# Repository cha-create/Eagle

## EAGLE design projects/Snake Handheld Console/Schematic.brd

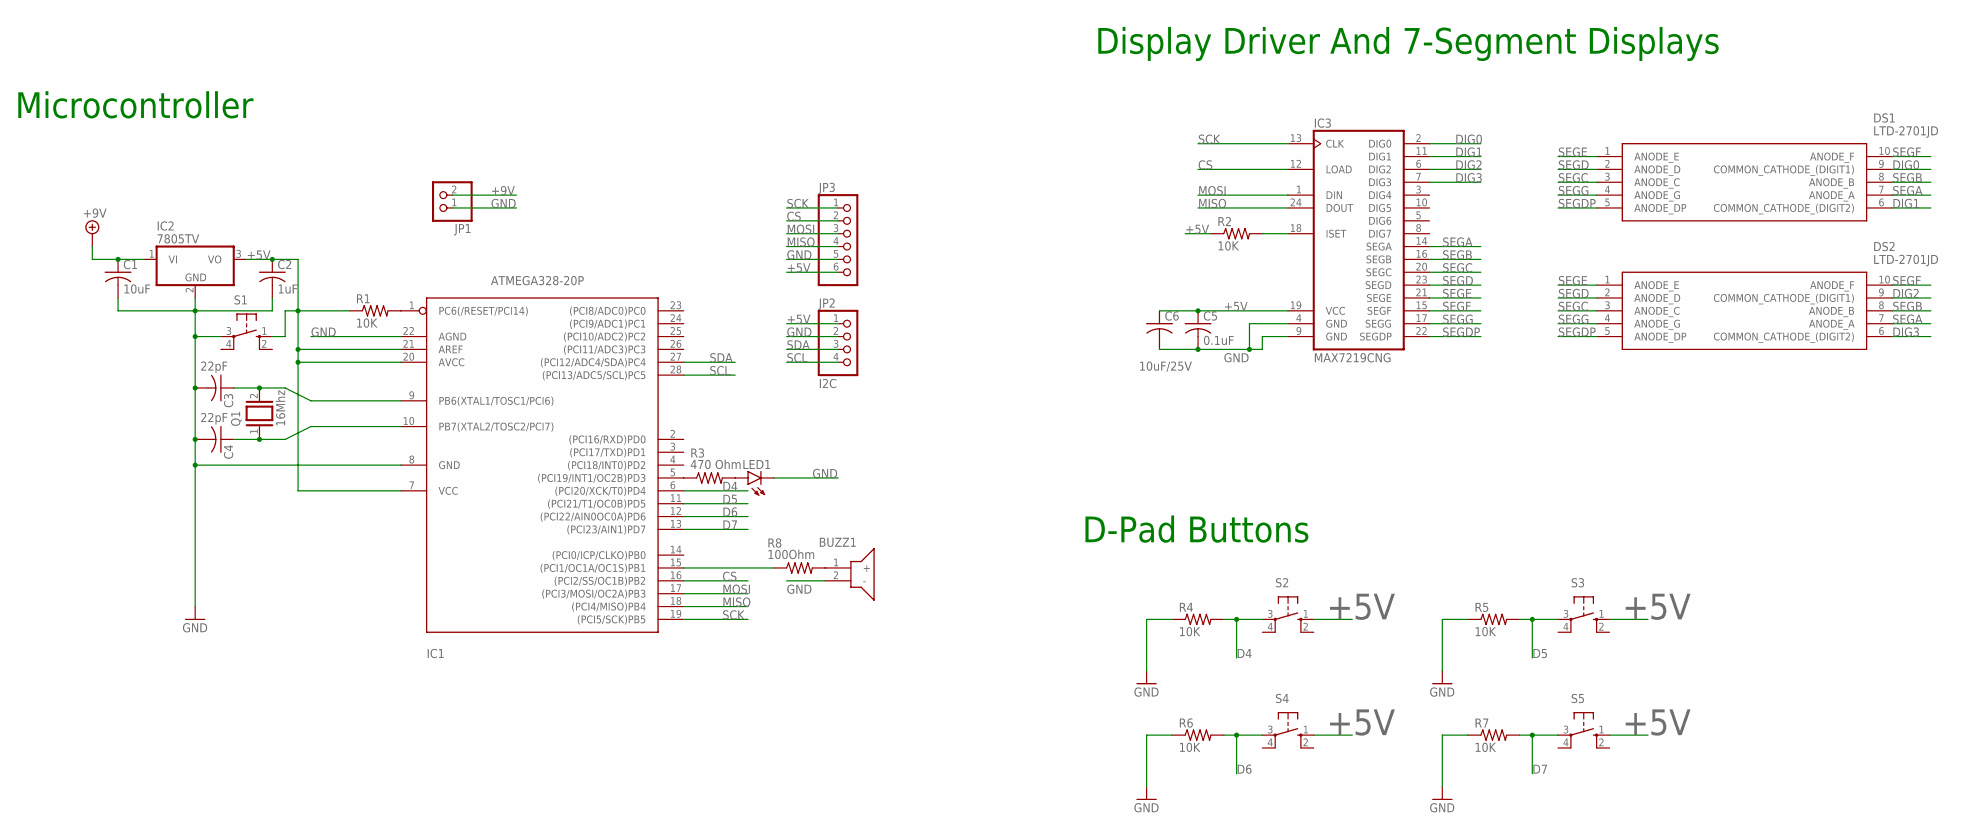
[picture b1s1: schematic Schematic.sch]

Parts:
BUZZ1: CMI-1295-0585T; CMI12950585T
C1: 10uF; C1206
C2: 1uF; C1206
C3, C4: 22pF; C1206
C5: 0.1uF; C1206
C6: 10uF/25V; C1206
DS1, DS2: LTD-2701JD; DIPS762W50P254L1502H635Q10N
IC1: ATMEGA328-20P; DIL28-3
IC2: 7805TV; TO220V
IC3: MAX7219CNG; DIL24-3
JP1: PINHD-1X2; 1X02
JP2: I2C; 1X04
JP3: PINHD-1X6; 1X06
LED1: LED5MM
Q1: 16Mhz; QS
R1, R2, R4, R5, R6, R7: 10K; R1206
R3: 470 Ohm; R1206
R8: 100Ohm; R1206
S1, S2, S3, S4, S5: 10-XX; B3F-10XX

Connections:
+5V: C2.1, C5.1, C6.1, IC1.7 (VCC), IC1.20 (AVCC), IC1.21 (AREF), IC2.3 (VO), IC3.19 (VCC), JP2.1, JP3.6, R1.1, R2.1, S1.1 (S), S2.1 (S), S3.1 (S), S4.1 (S), S5.1 (S)
+9V: C1.1, IC2.1 (VI), JP1.2
CS: IC1.16 ((PCI2/SS/OC1B)PB2), IC3.12 (LOAD), JP3.2
D4: IC1.6 ((PCI20/XCK/T0)PD4), R4.2, S2.3
D5: IC1.11 ((PCI21/T1/OC0B)PD5), R5.2, S3.3
D6: IC1.12 ((PCI22/AIN0OC0A)PD6), R6.2, S4.3
D7: IC1.13 ((PCI23/AIN1)PD7), R7.2, S5.3
DIG0: DS1.9 (COMMON_CATHODE_(DIGIT1)), IC3.2 (DIG0)
DIG1: DS1.6 (COMMON_CATHODE_(DIGIT2)), IC3.11 (DIG1)
DIG2: DS2.9 (COMMON_CATHODE_(DIGIT1)), IC3.6 (DIG2)
DIG3: DS2.6 (COMMON_CATHODE_(DIGIT2)), IC3.7 (DIG3)
GND: BUZZ1.2 (-), C1.2, C2.2, C3.2, C4.2, C5.2, C6.2, IC1.8 (GND), IC1.22 (AGND), IC2.2 (GND), IC3.4 (GND), IC3.9 (GND), JP1.1, JP2.2, JP3.5, LED1.K (C), R4.1, R5.1, R6.1, R7.1, S1.3
MISO: IC1.18 ((PCI4/MISO)PB4), IC3.24 (DOUT), JP3.4
MOSI: IC1.17 ((PCI3/MOSI/OC2A)PB3), IC3.1 (DIN), JP3.3
unnamed: IC3.18 (ISET), R2.2
unnamed: C3.1, IC1.9 (PB6(XTAL1/TOSC1/PCI6)), Q1.2
unnamed: C4.1, IC1.10 (PB7(XTAL2/TOSC2/PCI7)), Q1.1
unnamed: IC1.1 (PC6(/RESET/PCI14)), R1.2
unnamed: IC1.5 ((PCI19/INT1/OC2B)PD3), R3.1
unnamed: LED1.A, R3.2
unnamed: IC1.15 ((PCI1/OC1A/OC1S)PB1), R8.1
unnamed: BUZZ1.1 (+), R8.2
SCK: IC1.19 ((PCI5/SCK)PB5), IC3.13 (CLK), JP3.1
SCL: IC1.28 ((PCI13/ADC5/SCL)PC5), JP2.4
SDA: IC1.27 ((PCI12/ADC4/SDA)PC4), JP2.3
SEGA: DS1.7 (ANODE_A), DS2.7 (ANODE_A), IC3.14 (SEGA)
SEGB: DS1.8 (ANODE_B), DS2.8 (ANODE_B), IC3.16 (SEGB)
SEGC: DS1.3 (ANODE_C), DS2.3 (ANODE_C), IC3.20 (SEGC)
SEGD: DS1.2 (ANODE_D), DS2.2 (ANODE_D), IC3.23 (SEGD)
SEGDP: DS1.5 (ANODE_DP), DS2.5 (ANODE_DP), IC3.22 (SEGDP)
SEGE: DS1.1 (ANODE_E), DS2.1 (ANODE_E), IC3.21 (SEGE)
SEGF: DS1.10 (ANODE_F), DS2.10 (ANODE_F), IC3.15 (SEGF)
SEGG: DS1.4 (ANODE_G), DS2.4 (ANODE_G), IC3.17 (SEGG)

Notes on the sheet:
Display Driver And 7-Segment Displays
Microcontroller
D-Pad Buttons

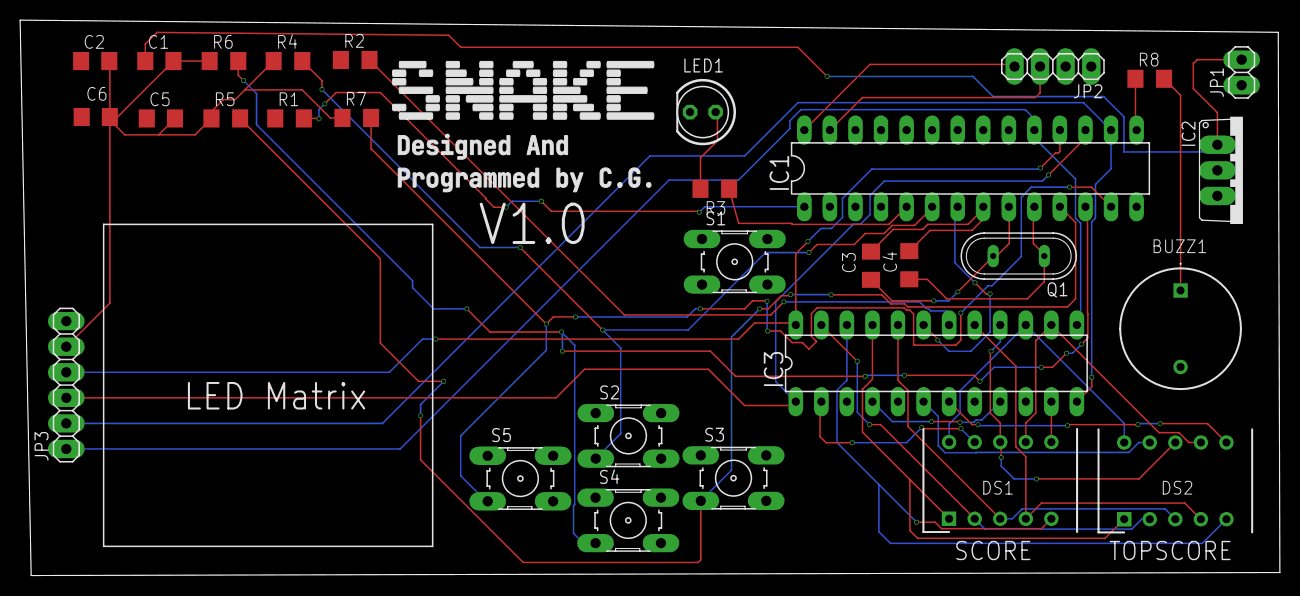
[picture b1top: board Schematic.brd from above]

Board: 2 copper layers, 125.2 x 55.2 mm, 30 parts (0 on the bottom side), 33 nets.

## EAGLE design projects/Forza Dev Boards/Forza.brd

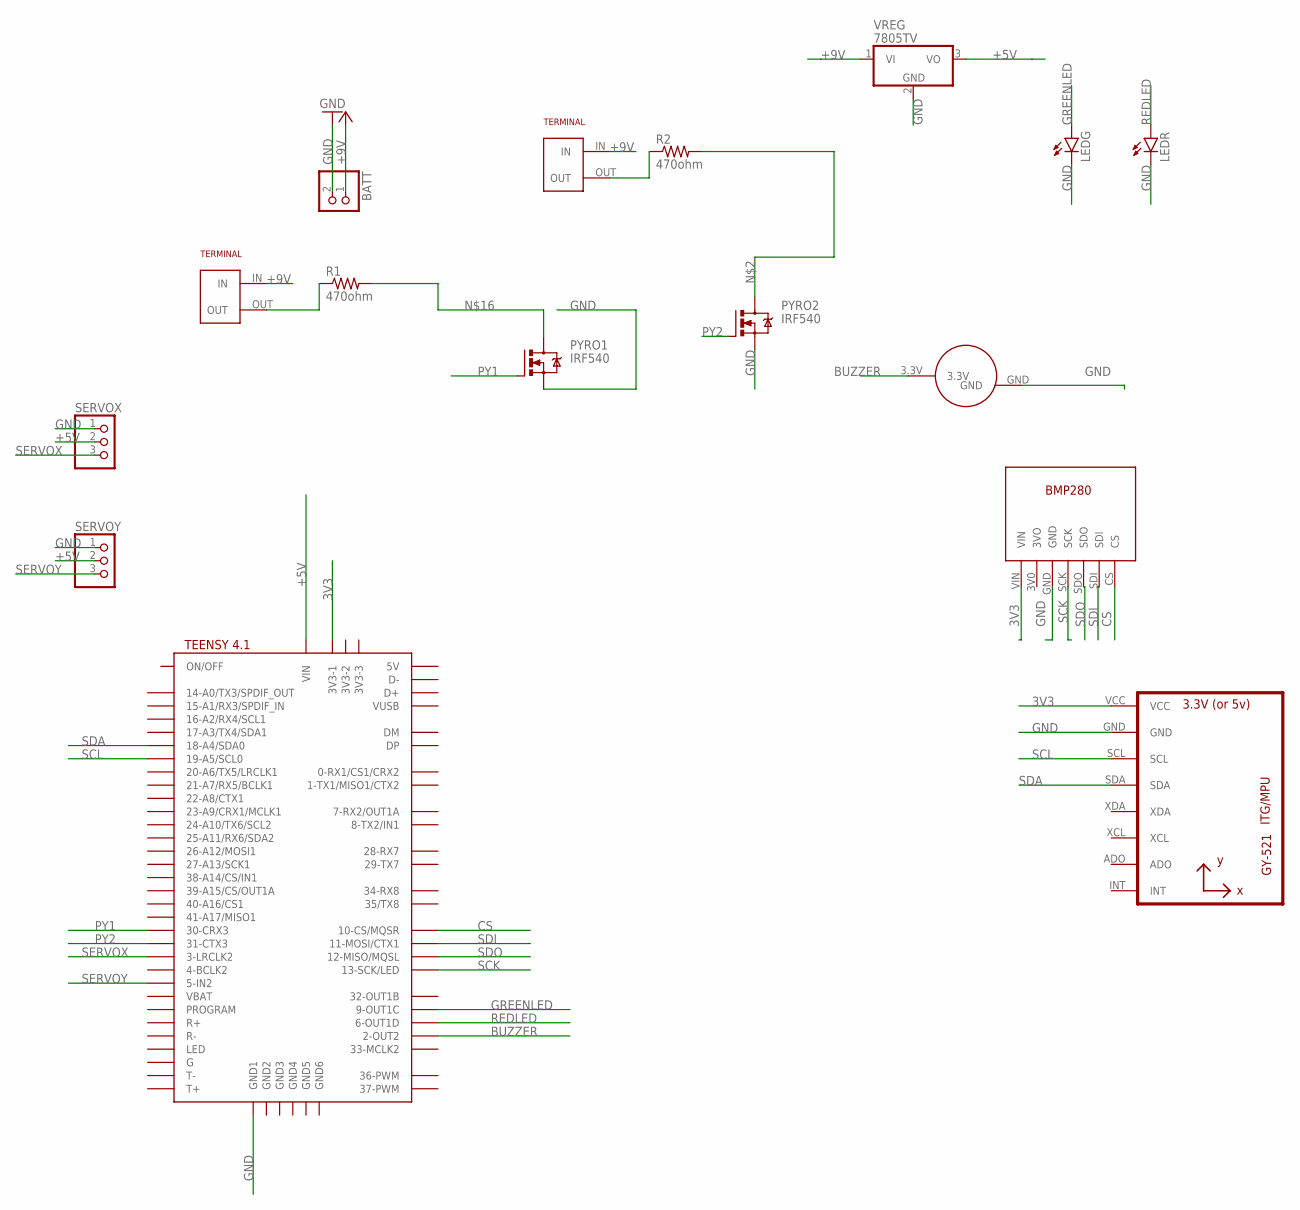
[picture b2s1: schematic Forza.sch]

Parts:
BATT: PINHD-1X2; 1X02
LEDG: LED5MM
LEDR: LED5MM
PY1, PY2: SCREWTERMINAL
PYRO1, PYRO2: IRF540; TO220BV
R1, R2: 470ohm; 0204/7
SERVOX: PINHD-1X3; 1X03
SERVOY: PINHD-1X3; 1X03
U1: GY-521MPU6050; GY-521
U$2: BUZZER
U$3: TEENSY41
U$4: BMP280
VREG: 7805TV; TO220V

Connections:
3V3: U1.VCC, U$3.3V3-1, U$4.VIN
+5V: SERVOX.2, SERVOY.2, U$3.VIN, VREG.3 (VO)
+9V: BATT.1, PY1.IN, PY2.IN, VREG.1 (VI)
BUZZER: U$2.3.3V, U$3.2-OUT2
CS: U$3.10-CS\MQSR (10-CS/MQSR), U$4.CS
GND: BATT.2, LEDG.K (C), LEDR.K (C), PYRO1.S, PYRO2.S, SERVOX.1, SERVOY.1, U1.GND, U$2.GND, U$3.GND1, U$4.GND, VREG.2 (GND)
GREENLED: LEDG.A, U$3.9-OUT1C
unnamed: PY1.OUT, R1.1
unnamed: PYRO2.D, R2.2
unnamed: PY2.OUT, R2.1
unnamed: PYRO1.D, R1.2
PY1: PYRO1.G, U$3.30-CRX3
PY2: PYRO2.G, U$3.31-CTX3
REDLED: LEDR.A, U$3.6-OUT1D
SCK: U$3.13-SCK/LED, U$4.SCK
SCL: U1.SCL, U$3.19-A5/SCL0
SDA: U1.SDA, U$3.18-A4/SDA0
SDI: U$3.11-MOSI/CTX1, U$4.SDI
SDO: U$3.12-MISO/MQSL, U$4.SDO
SERVOX: SERVOX.3, U$3.3-LRCLK2
SERVOY: SERVOY.3, U$3.5-IN2

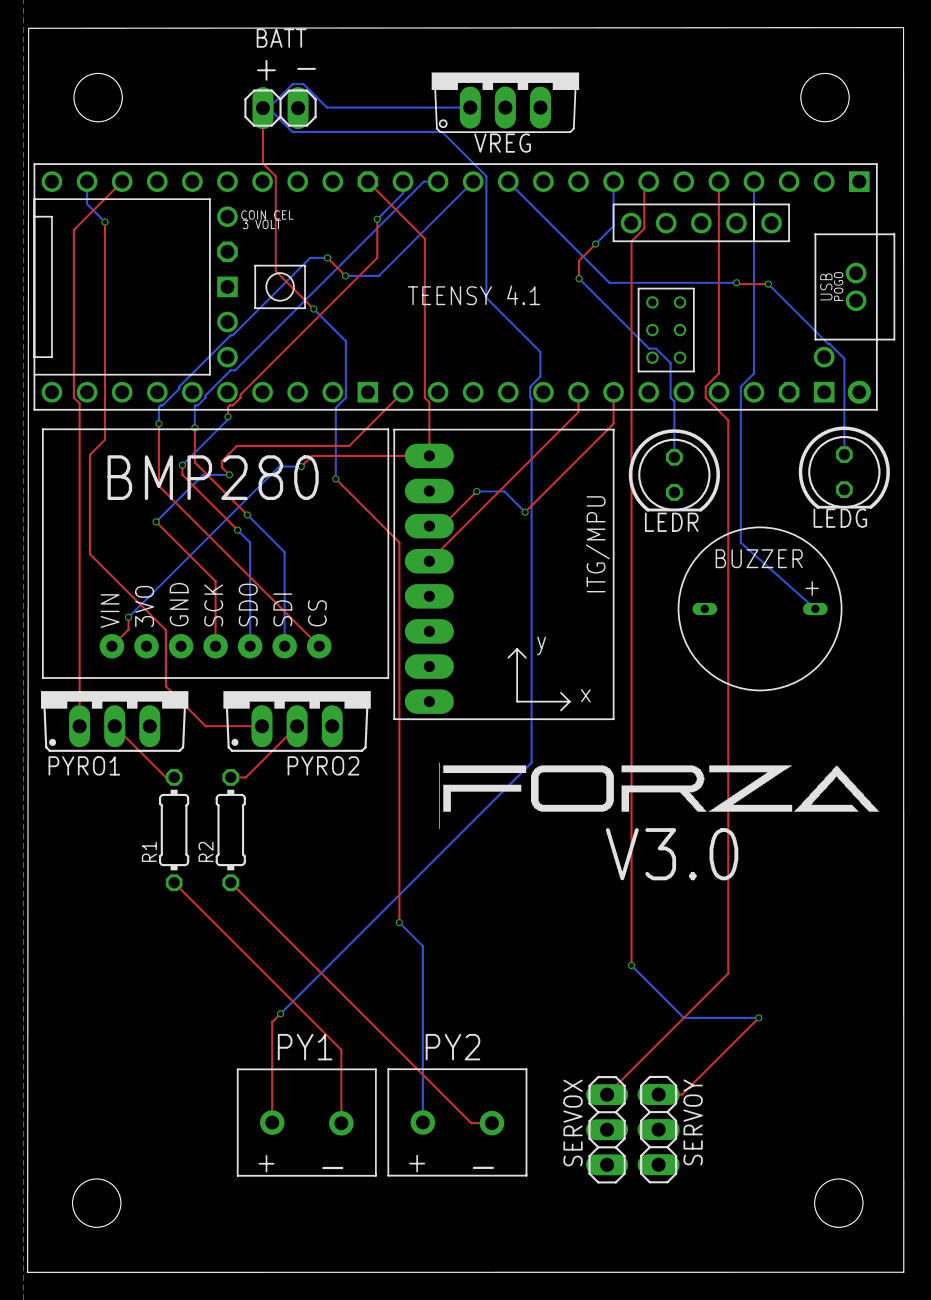
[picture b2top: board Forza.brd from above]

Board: 2 copper layers, 63.4 x 90.1 mm, 16 parts (0 on the bottom side), 21 nets.

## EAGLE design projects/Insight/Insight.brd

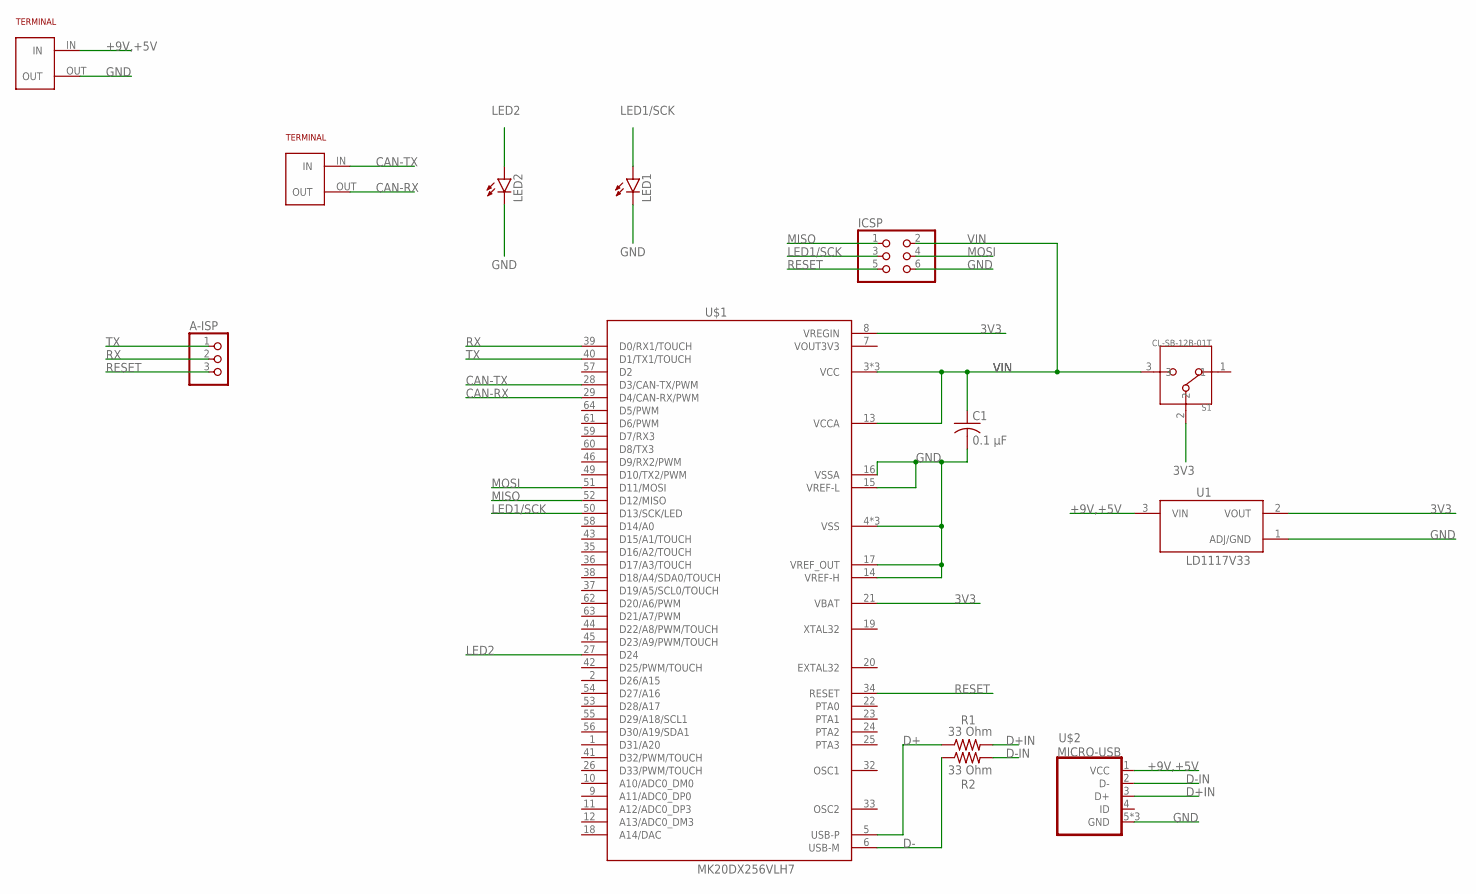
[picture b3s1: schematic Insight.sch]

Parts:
A-ISP: PINHD-1X3; 1X03
C1: 0.1 µF; C0805
ICSP: PINHD-2X3; 2X03
LED1, LED2: LED5MM
R1, R2: 33 Ohm; R1206
S1: CL-SB-12B-01T; CL-SB-12B
U1: LD1117V33; TO255P1020X450X1968-3
U$1: MK20DX256VLH7; QFP50P1200X1200X160-64N
U$2: MICRO-USB
U$3, U$4: SCREWTERMINAL

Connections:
3V3: S1.2, U1.2 (VOUT), U$1.8 (VREGIN), U$1.21 (VBAT)
+9V,+5V: U1.3 (VIN), U$2.1 (VCC), U$3.IN
CAN-RX: U$1.29 (D4/CAN-RX/PWM), U$4.OUT
CAN-TX: U$1.28 (D3/CAN-TX/PWM), U$4.IN
D+: R1.1, U$1.5 (USB-P)
D+IN: R1.2, U$2.3 (D+)
D-: R2.1, U$1.6 (USB-M)
D-IN: R2.2, U$2.2 (D-)
GND: C1.2, ICSP.6, LED1.K (C), LED2.K (C), U1.1 (ADJ/GND), U$1.4 (VSS), U$1.14 (VREF-H), U$1.15 (VREF-L), U$1.16 (VSSA), U$1.17 (VREF_OUT), U$1.31 (VSS), U$1.47 (VSS), U$2.5 (GND), U$2.GND1 (GND), U$2.GND2 (GND), U$3.OUT
LED1/SCK: ICSP.3, LED1.A, U$1.50 (D13/SCK/LED)
LED2: LED2.A, U$1.27 (D24)
MISO: ICSP.1, U$1.52 (D12/MISO)
MOSI: ICSP.4, U$1.51 (D11/MOSI)
RESET: A-ISP.3, ICSP.5, U$1.34 (RESET)
RX: A-ISP.2, U$1.39 (D0/RX1/TOUCH)
TX: A-ISP.1, U$1.40 (D1/TX1/TOUCH)
VIN: C1.1, ICSP.2, S1.3, U$1.3 (VCC), U$1.13 (VCCA), U$1.30 (VCC), U$1.48 (VCC)

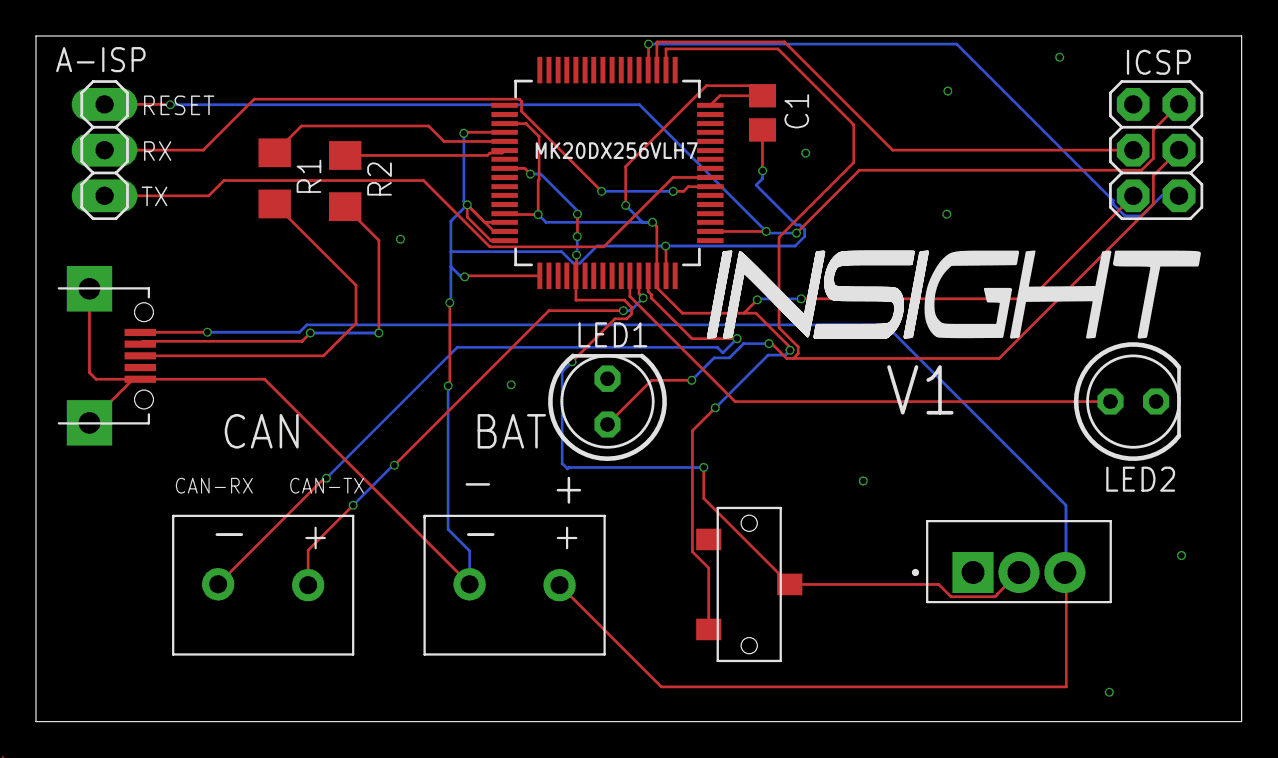
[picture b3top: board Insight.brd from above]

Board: 2 copper layers, 67.0 x 38.1 mm, 13 parts (0 on the bottom side), 17 nets.

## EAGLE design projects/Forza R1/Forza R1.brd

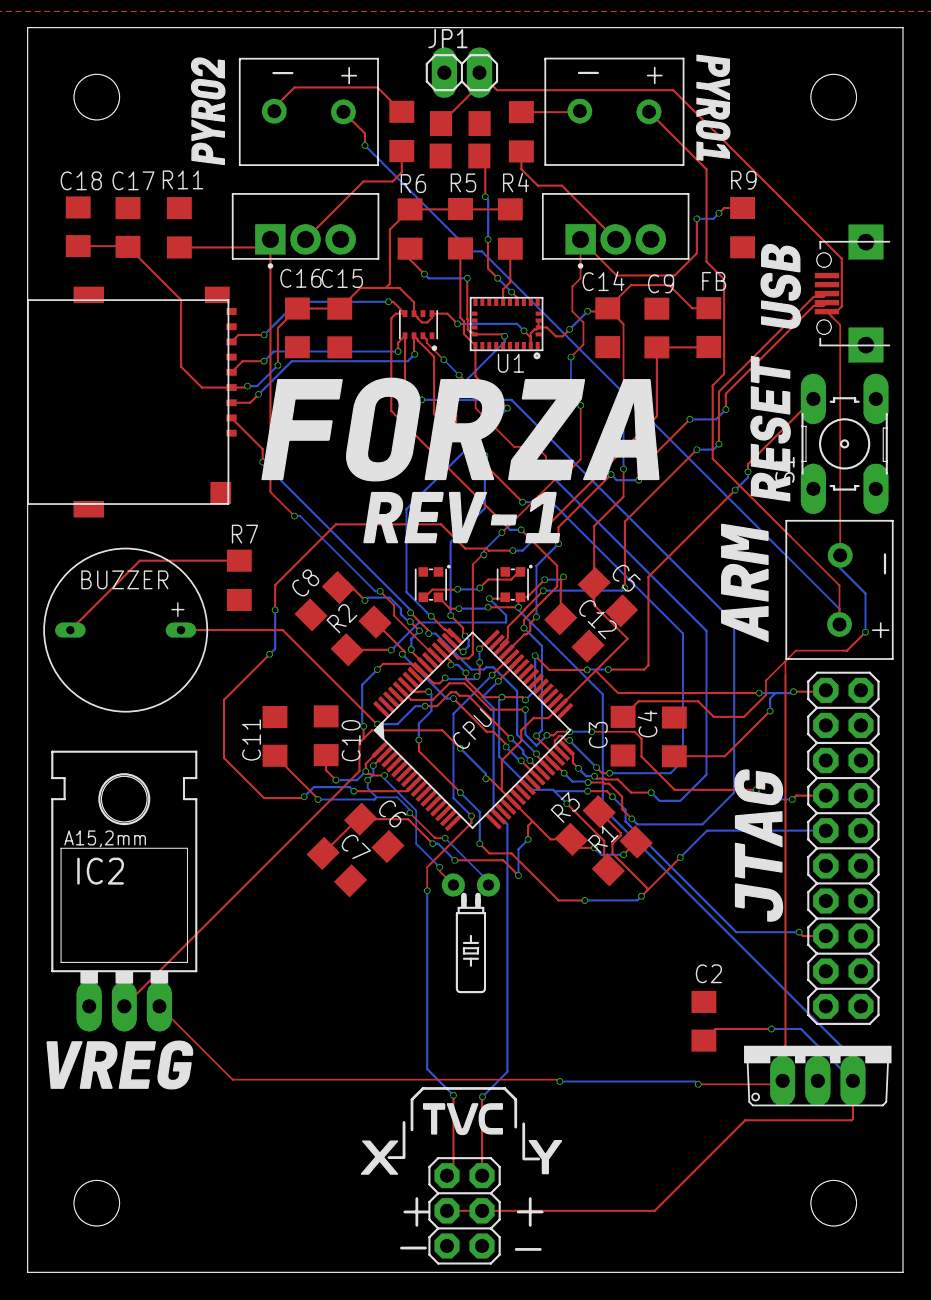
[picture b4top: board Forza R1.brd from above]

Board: 2 copper layers, 63.3 x 90.0 mm, 50 parts (0 on the bottom side), 36 nets.

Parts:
C1, C3, C4: 10uf; C1206
C2, C9: 1uf; C1206
C5, C6, C7, C8, C13, C14, C17, C18: 0.1uf; C1206
C10, C11: 15pf; C1206
C12: 1000uf; C1206
C15, C16: 100nF; C1206
D1, D2: WS2812_2020; WS2812-2020
FB: 30 Ohm; C1206
IC1: 7805TV; TO220V
IC2: LD117AV; TO220L1
JP1: 1X02
JP2: 2X10
JP3: 2X03
Q5, Q6: IRLZ44N; TO254P1054X469X1930-3
R1, R4, R5, R6: 10K; R1206
R2, R9, R11: 470Ohm; R1206
R3: 1K; R1206
R7: 100Ohm; R1206
R8, R10: 1Ohm; R1206
S1: B3F-10XX
U1: BNO055; LGA28R50P4X10_380X520X100
U2: BMP280; XDCR_BMP280
U$1: ATSAMD2164TQFP; SAMD21
U$2: BUZZER
U$3: MICRO-USB
U$4, U$5, U$8: SCREWTERMINAL
U$7: MICROSD-PUSH-OUT
Y1: 32.768kHz; CRYSTAL-PTH-2X6-CYL

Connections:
3.3V: C4.1, C5.1, C6.1, C7.1, C14.2, C15.1, C16.2, C17.1, C18.1, FB.1, IC2.2, JP2.1, R1.2, R3.1, R4.2, R5.2, R6.2, U1.3, U1.4, U1.28, U2.6, U2.8, U$1.VDDIN, U$1.VDDIO, U$1.VDDIO1, U$1.VDDIO2, U$7.4
5V: C2.1, C12.1, D1.VCC, D2.VCC, IC1.3, JP3.3, JP3.4
7.4V: C1.1, C3.1, IC1.1, IC2.3, JP1.2, U$3.1, U$8.IN
7.4VPS: U$4.OUT, U$5.OUT, U$8.OUT
CS: U2.2, U$1.PA15
CSCARD: U$1.PB15, U$7.2
DM: U$1.PA24, U$3.2
DP: U$1.PA25, U$3.3
GND: C1.2, C2.2, C3.2, C4.2, C5.2, C6.2, C7.2, C8.1, C9.2, C10.1, C11.1, C12.2, C13.1, C14.1, C15.2, C16.1, C17.2, C18.2, D1.GND, D2.GND, IC1.2, IC2.1, JP1.1, JP2.4, JP2.6, JP2.8, JP2.10, JP2.12, JP2.14, JP2.16, JP2.18, JP2.20, JP3.5, JP3.6, Q5.3, Q6.3, R7.1, R9.1, R11.1, S1.4, U1.2, U1.5, U1.6, U1.10, U1.15, U1.16, U1.17, U1.18, U1.25, U2.1, U2.7, U$1.GND, U$1.GND1, U$1.GND2, U$1.GND3, U$1.GNDANA, U$3.5, U$3.GND1, U$3.GND2, U$7.6, U$7.G1, U$7.G2, U$7.G3, U$7.G4
LEDIN: R2.2, U$1.PB13
MISO: U2.5, U$1.PA13, U$7.7
MOSI: U2.3, U$1.PA14, U$7.3
unnamed: C8.2, U$1.VDDCORE
unnamed: C9.1, FB.2, U$1.VDDANA
unnamed: D1.DO, D2.DI
unnamed: C11.2, U$1.PA01, Y1.1
unnamed: C10.2, U$1.PA00, Y1.2
unnamed: U$1.PB14, U$2.3.3V
unnamed: D1.DI, R2.1
unnamed: R7.2, U$2.GND
unnamed: R8.2, U$4.IN
unnamed: Q5.2, R8.1
unnamed: R10.2, U$5.IN
unnamed: Q6.2, R10.1
unnamed: C13.2, U1.9
unnamed: R4.1, U1.11
PY1: Q5.1, R9.2, U$1.PA27
PY2: Q6.1, R11.2, U$1.PA28
RESET: JP2.15, R1.1, S1.2, U$1.RESET
SCK: U2.4, U$1.PA12, U$7.5
SCL: R6.1, U1.19, U$1.PB23
SDA: R5.1, U1.20, U$1.PB22
SWCLK: JP2.9, R3.2, U$1.PB30
SWDIO: JP2.7, U$1.PB31
TVCX: JP3.1, U$1.PA23
TVCY: JP3.2, U$1.PA22

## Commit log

2023-07-29 init

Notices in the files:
parts and their libraries:
SparkFun-LED: Licensing: Creative Commons ShareAlike 4.0 International - https://creativecommons.org/licenses/by-sa/4.0
